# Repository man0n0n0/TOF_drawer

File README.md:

# configuration mode notice 

- turn off the device by unplugging it
- **keep** the config button pressed
- plug the device
  (while started you can release the button)
- connect on the wifi hotspot
  SSID : **"drawer-config"**
  PASSWORD : **"admin123"**
- while connected go to **192.168.4.1**
- modify values and **Save settings**
- the drawer should automatically restart in "main mode" with updated values

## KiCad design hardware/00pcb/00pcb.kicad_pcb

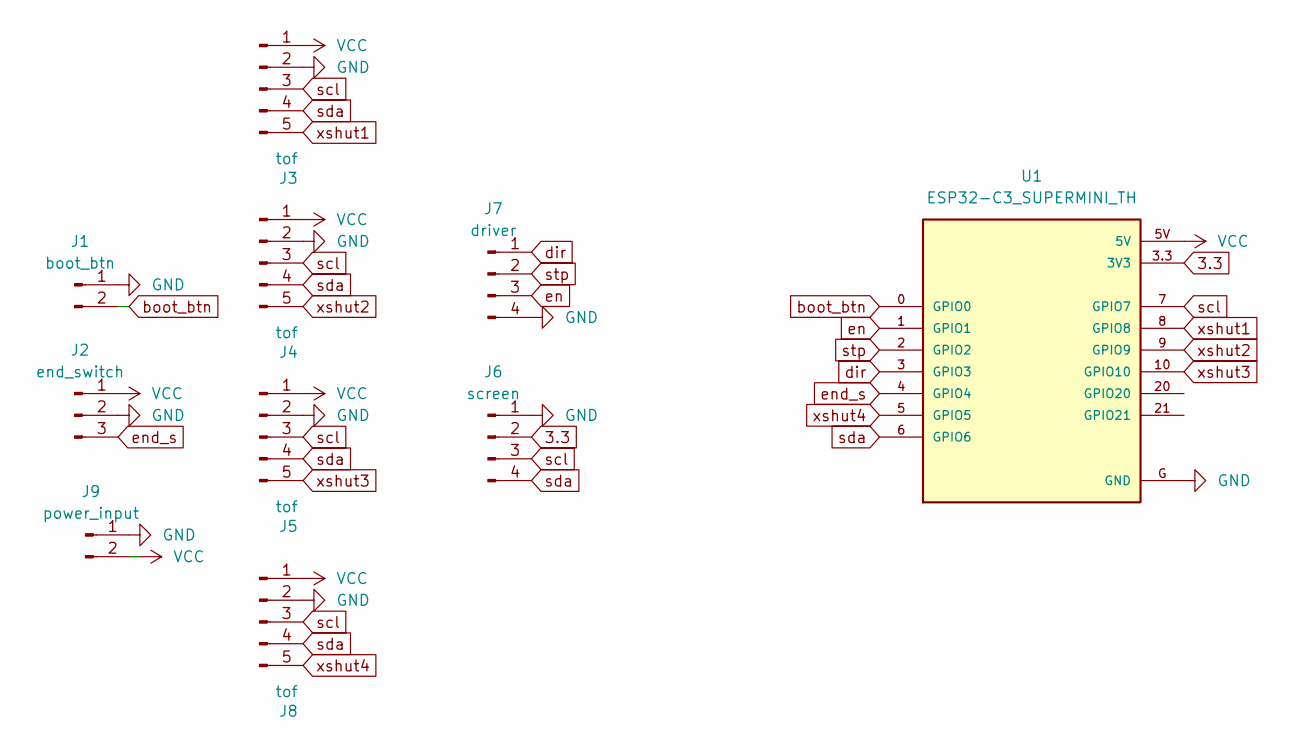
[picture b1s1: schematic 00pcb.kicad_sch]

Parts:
J1: boot_btn; PinHeader_1x02_P2.54mm_Vertical
J2: end_switch; PinHeader_1x03_P2.54mm_Vertical
J3, J4, J5, J8: tof; JST_XH_B5B-XH-A_1x05_P2.50mm_Vertical
J6: screen; PinHeader_1x04_P2.54mm_Vertical
J7: driver; JST_XH_B4B-XH-A_1x04_P2.50mm_Vertical
J9: power_input; PinHeader_1x02_P2.54mm_Vertical
U1: ESP32-C3_SUPERMINI_TH; MODULE_ESP32-C3_SUPERMINI

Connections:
3.3: J6.2, U1.3.3 (3V3)
GND: J1.1, J2.2, J3.2, J4.2, J5.2, J6.1, J7.4, J8.2, J9.1, U1.G (GND)
VCC: J2.1, J3.1, J4.1, J5.1, J8.1, J9.2, U1.5V
boot_btn: J1.2, U1.0 (GPIO0)
dir: J7.1, U1.3 (GPIO3)
en: J7.3, U1.1 (GPIO1)
end_s: J2.3, U1.4 (GPIO4)
scl: J3.3, J4.3, J5.3, J6.3, J8.3, U1.7 (GPIO7)
sda: J3.4, J4.4, J5.4, J6.4, J8.4, U1.6 (GPIO6)
stp: J7.2, U1.2 (GPIO2)
xshut1: J3.5, U1.8 (GPIO8)
xshut2: J4.5, U1.9 (GPIO9)
xshut3: J5.5, U1.10 (GPIO10)
xshut4: J8.5, U1.5 (GPIO5)

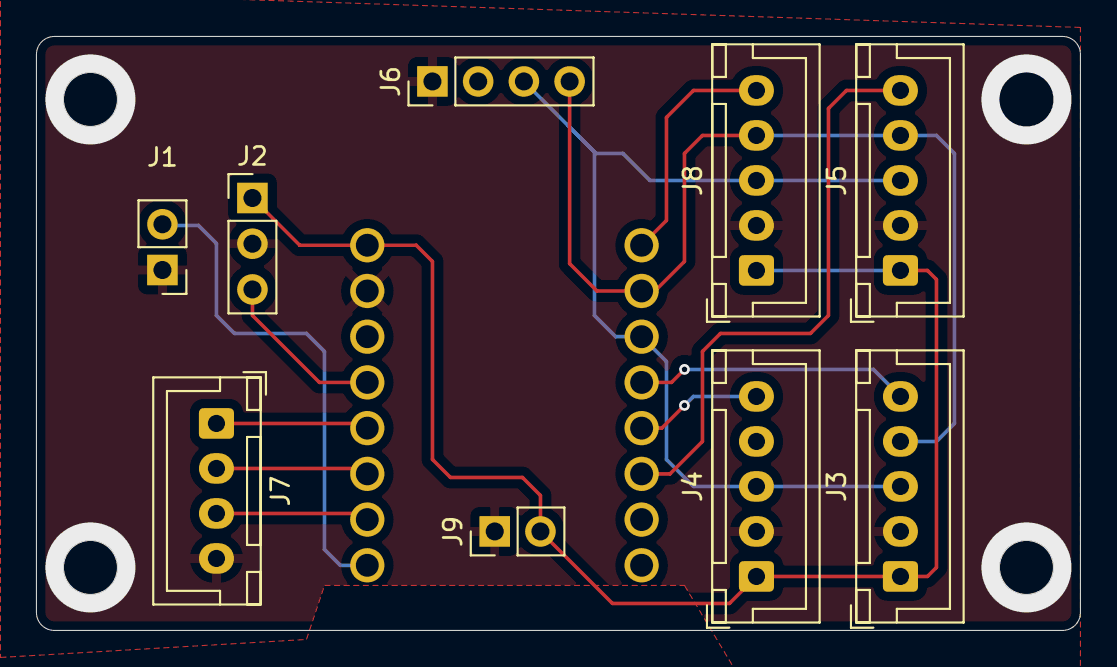
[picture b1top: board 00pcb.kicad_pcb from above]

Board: 2 copper layers, 58.0 x 33.0 mm, 10 parts (1 on the bottom side), 14 nets.

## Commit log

2025-04-02 added pulley bracket
2025-04-03 added hrdwr elements
2025-04-04 new addition
2025-04-07 redme edit
2025-04-07 pulley holder edit + new code on construction
2025-04-08 boot led for c3 + html
2025-04-08 config management : claude edit
2025-04-08 accelration management
2025-04-09 added pcb
2025-04-14 new driver + 3 tof
2025-04-21 radme + pcb
2025-04-21 ld2410 added + en maanegement + logid minorrework
2025-04-21 network logic
2025-04-21 import external html
2025-04-21 light config edit (claude edit)
2025-04-21 json managmeent + code length opitimisation (claude help)
2025-04-21 logid adjustement
2025-04-23 edited library and print example (claudio)
2025-04-23 radar new lib implementation
2025-04-23 TODO:fix timing + uart maangement
2025-04-24 threading of uart radar (claude edit)
2025-04-24 config logic edition + main threaded merged
2025-04-24 added wit_inside variable + proper pinout for endswitch
2025-04-24 proper values
2025-04-24 tempo + minor estetic changes
2025-04-28 new lib + test case (claude)
2025-05-14 hardawre din rail + claude edit for new dm332t lib
2025-05-14 vl53l1x support
2025-05-14 detecting staitonary with ld24110
2025-05-15 added track mm , enhanced dm332t lib, enhanced acceleration management
    working main code
2025-05-17 working main mode (with latency) + dm332t lib withotu accel profile
2025-05-19 dual uart using ( 2 radar module) + dual core with regular esp32
2025-05-20 hardawre (sensor bracket) + optimisation in nonedex code
2025-05-20 struct optimization
2025-05-20 using previous stepper driver (software)
2025-05-21 arduino version : faster process
2025-05-22 d_out value + hardware
2025-05-28 hardware rewrok
2025-05-28 hardware + blocking out drawer
2025-05-28 gpio code !!
2025-05-30 dm332t
2025-05-30 Update README.md (configuration notice)
2025-06-03 last minute edit
